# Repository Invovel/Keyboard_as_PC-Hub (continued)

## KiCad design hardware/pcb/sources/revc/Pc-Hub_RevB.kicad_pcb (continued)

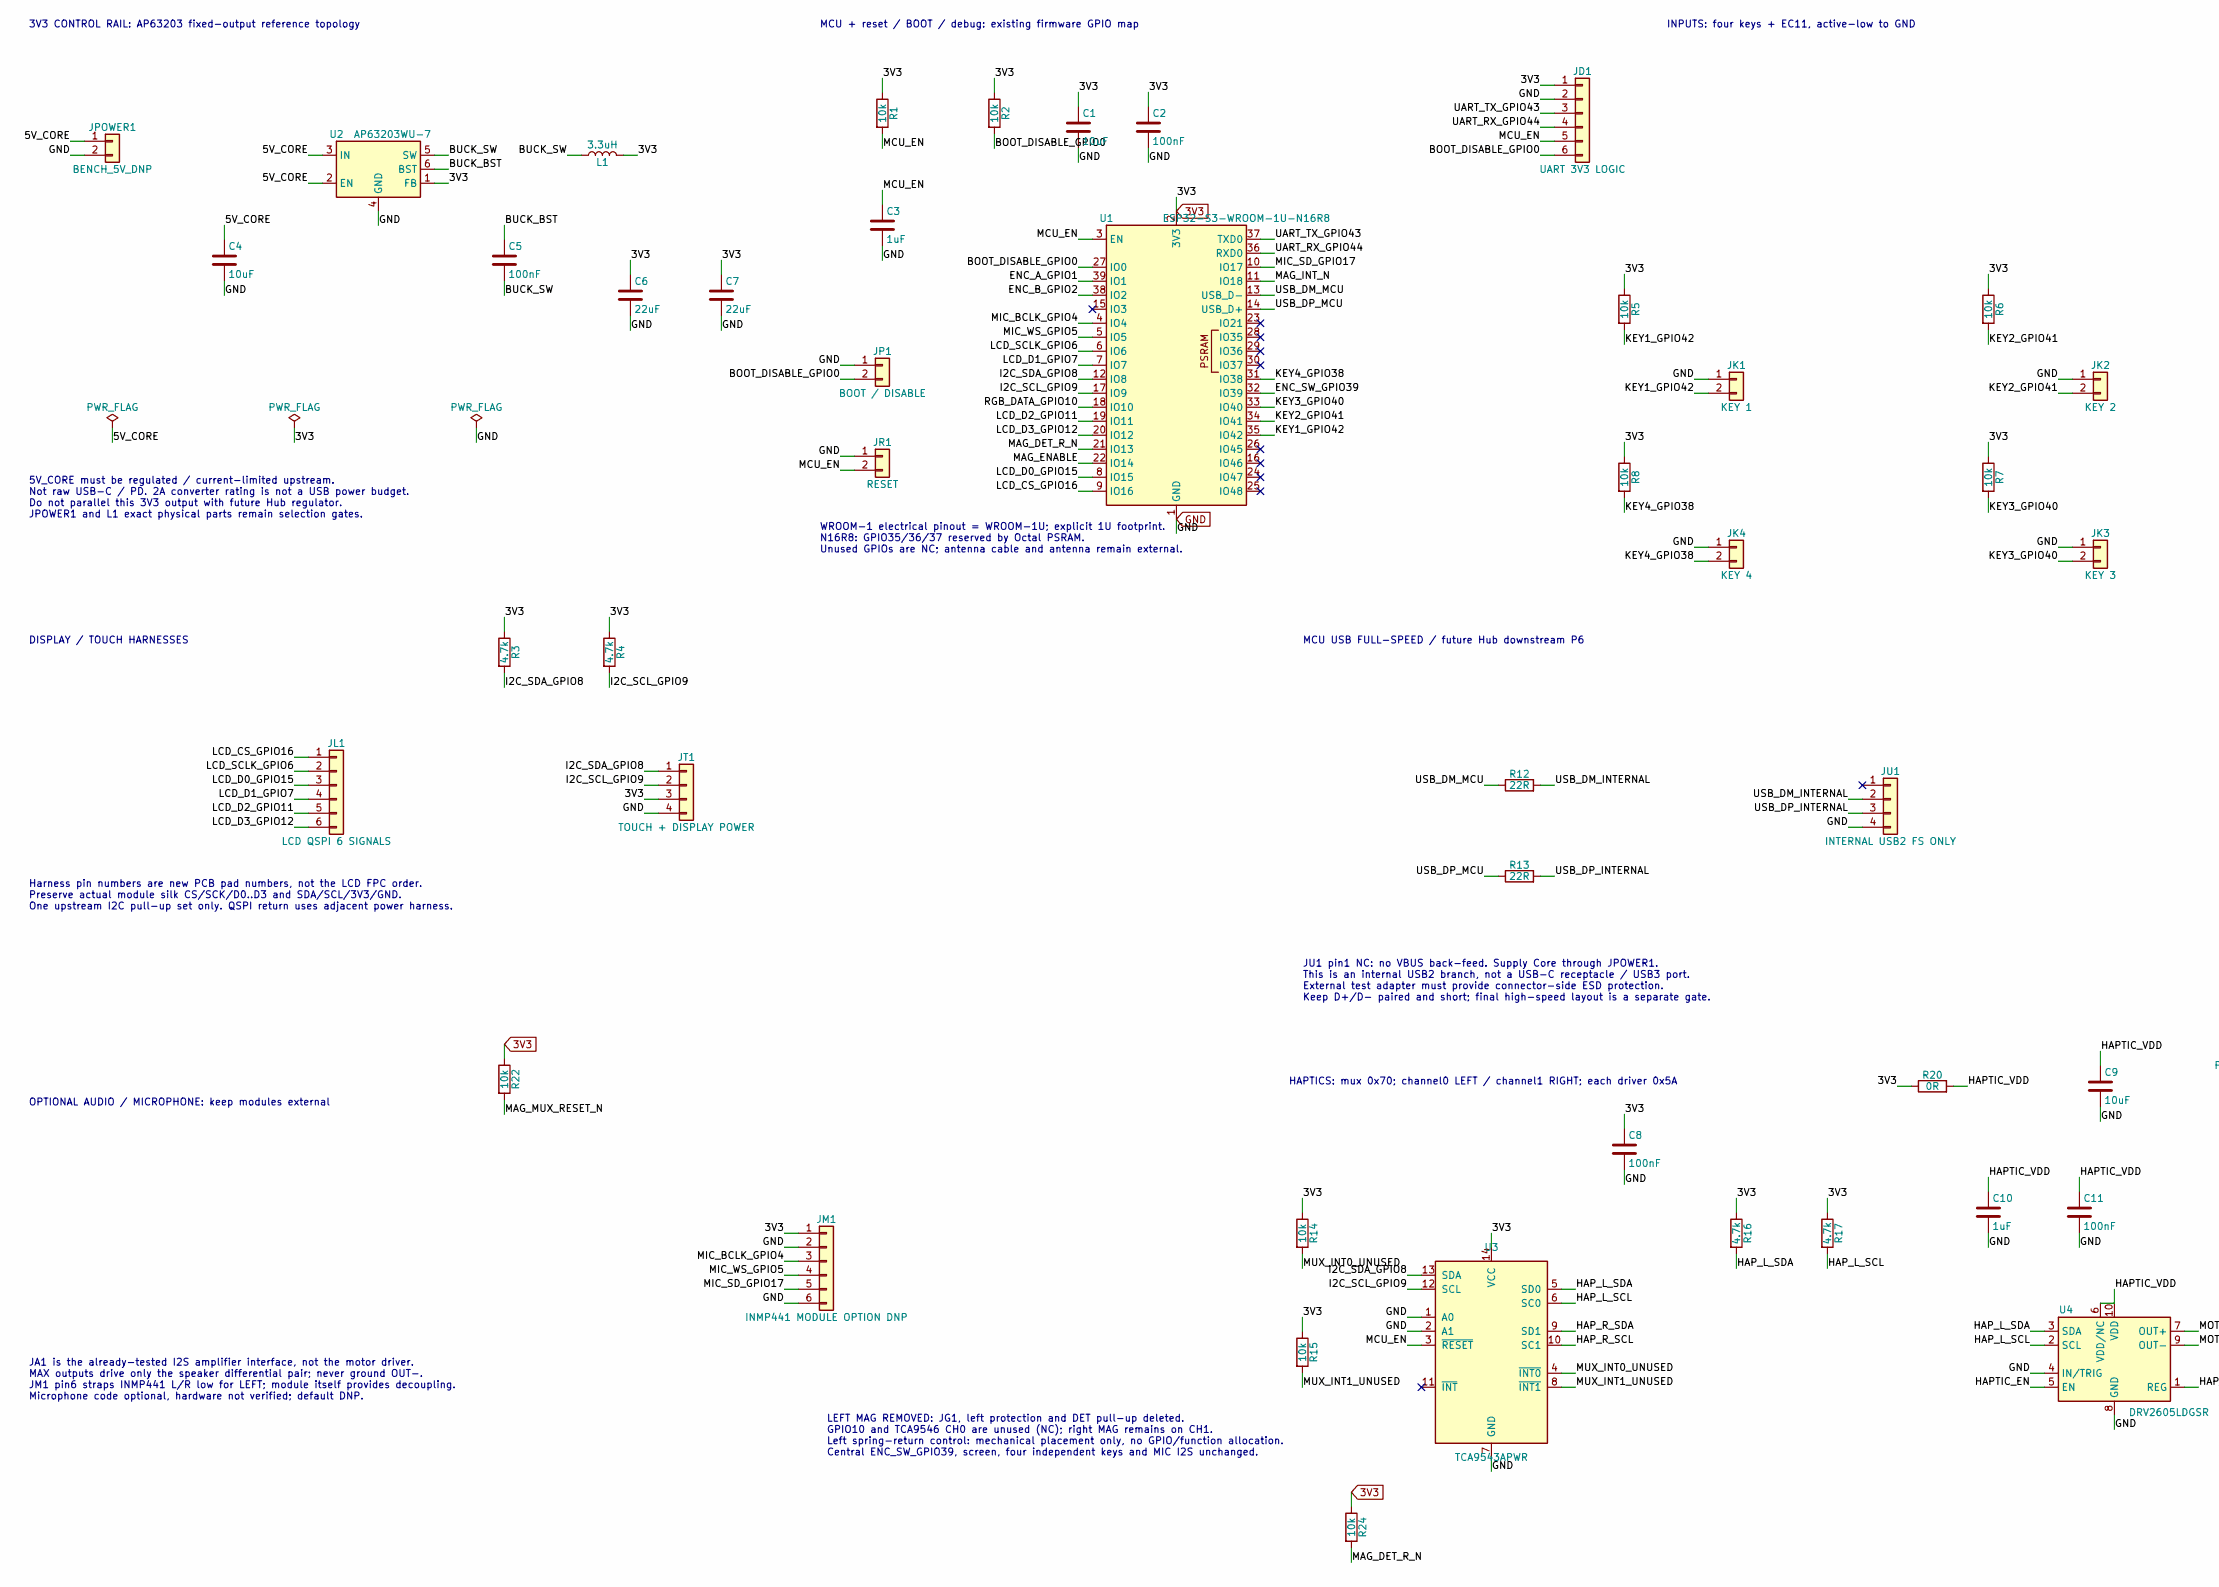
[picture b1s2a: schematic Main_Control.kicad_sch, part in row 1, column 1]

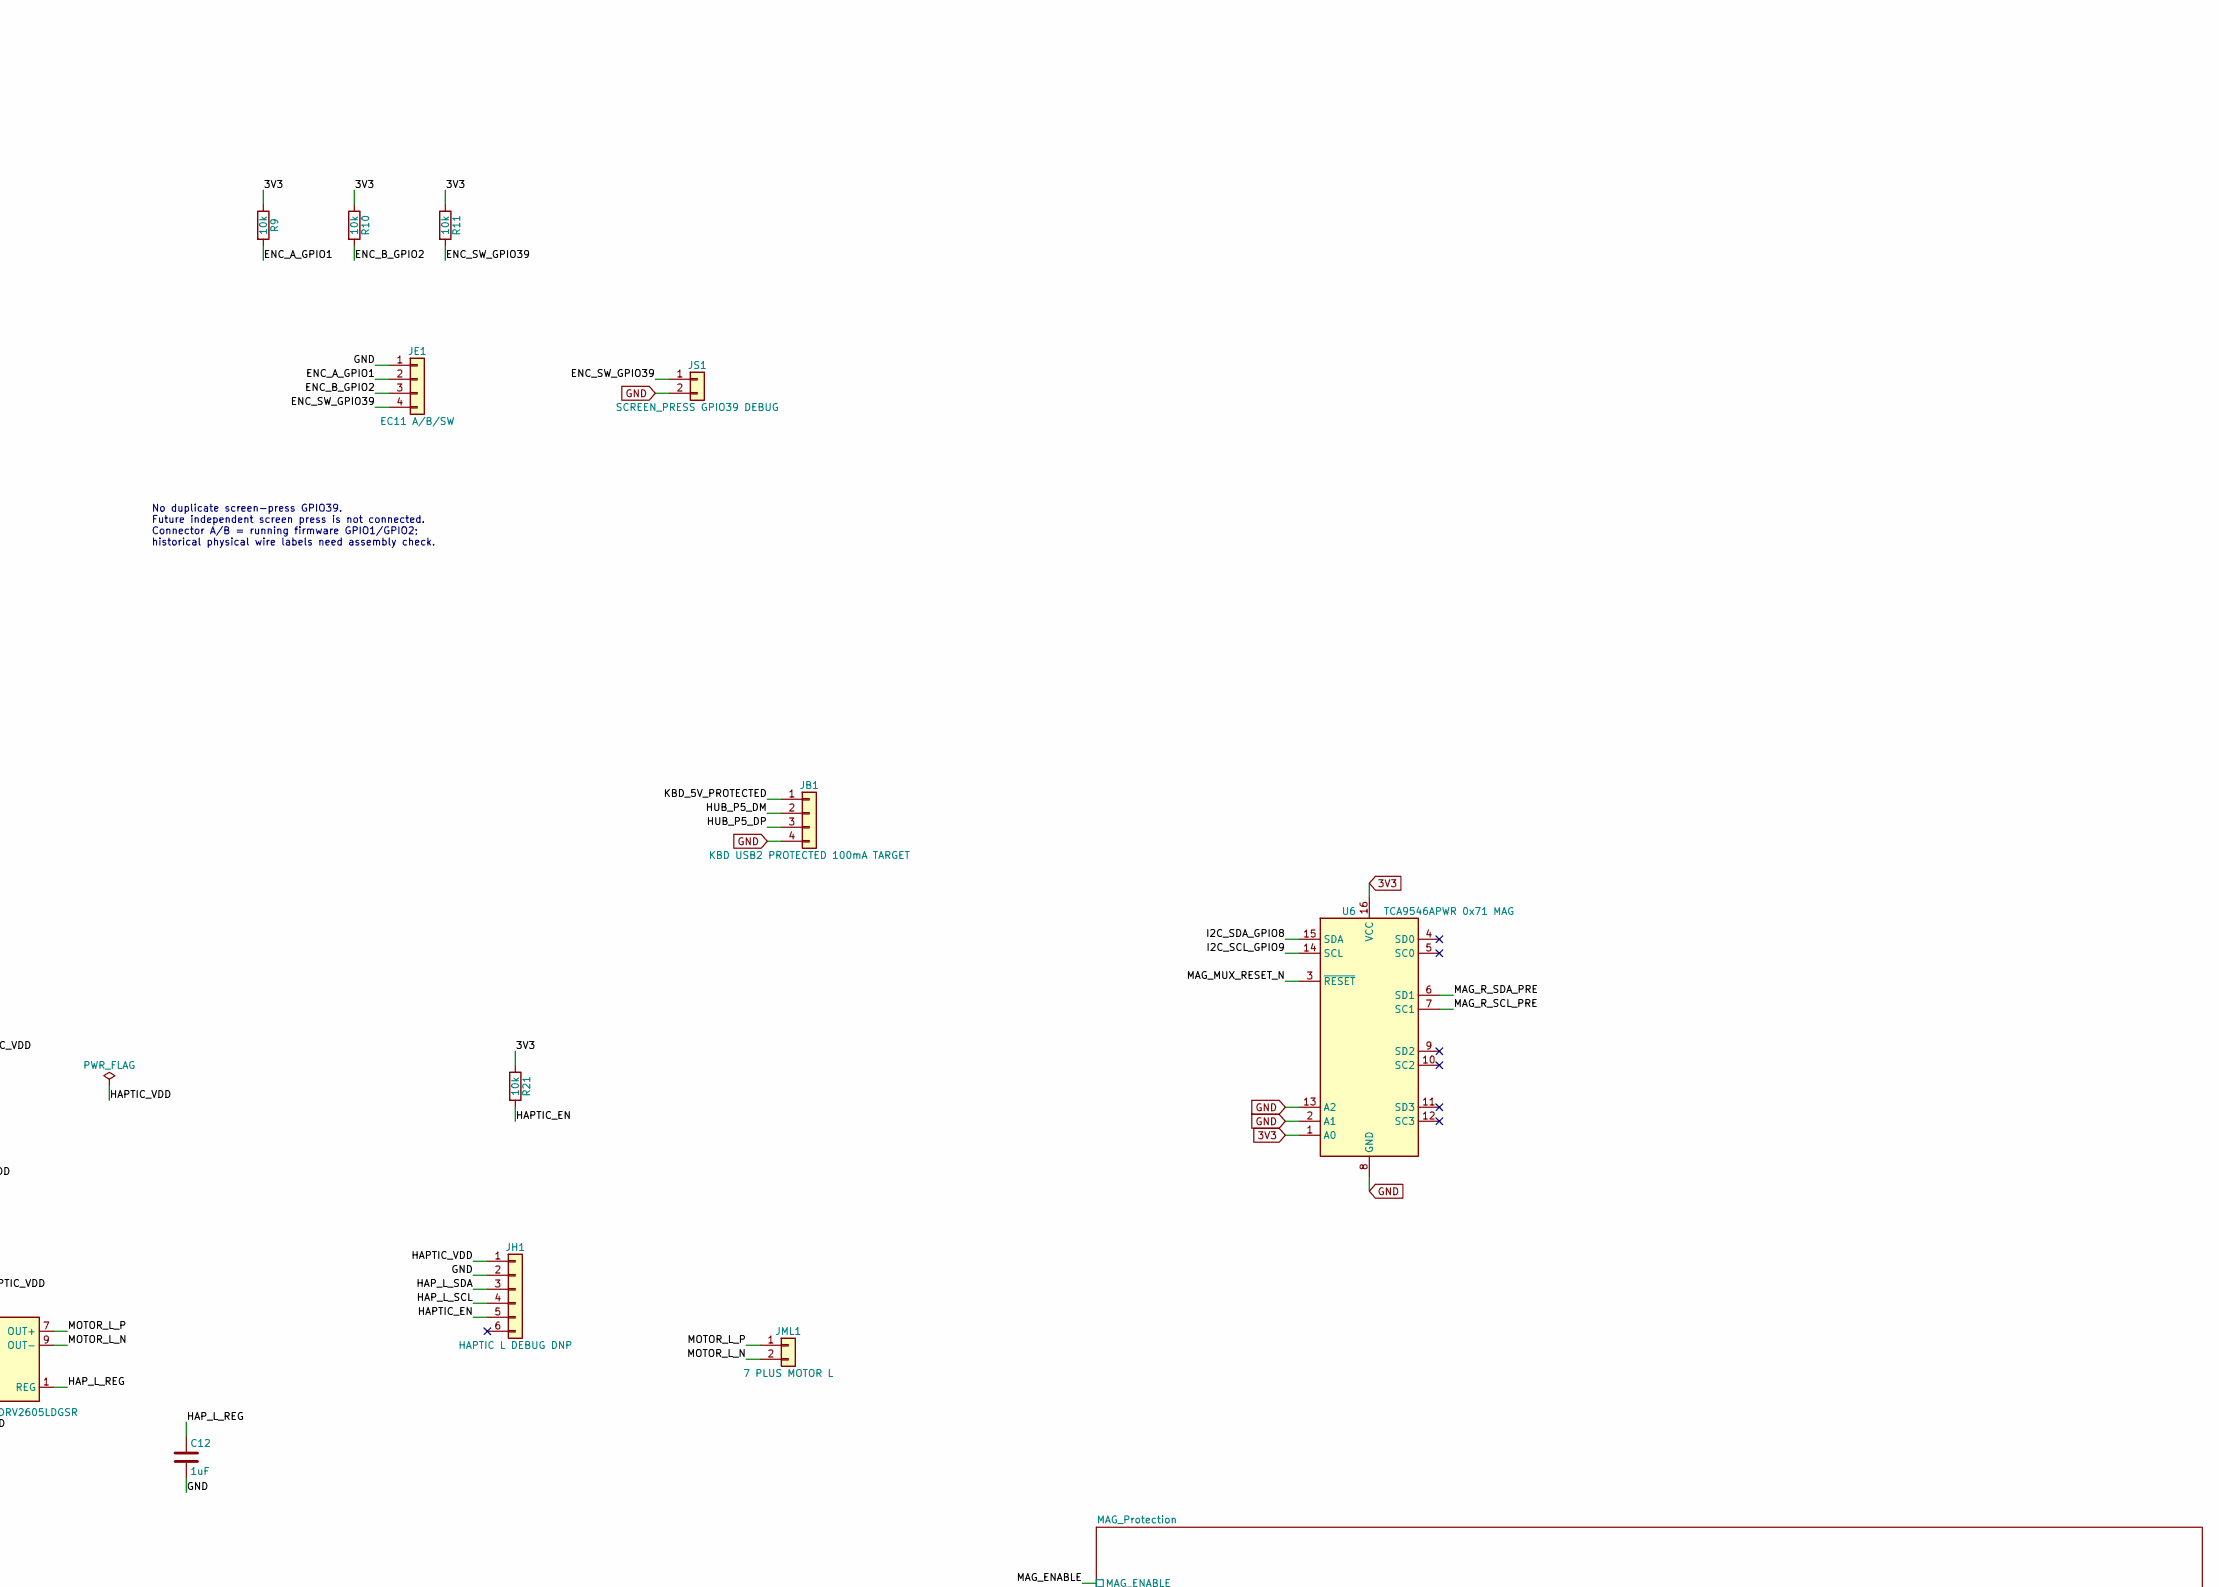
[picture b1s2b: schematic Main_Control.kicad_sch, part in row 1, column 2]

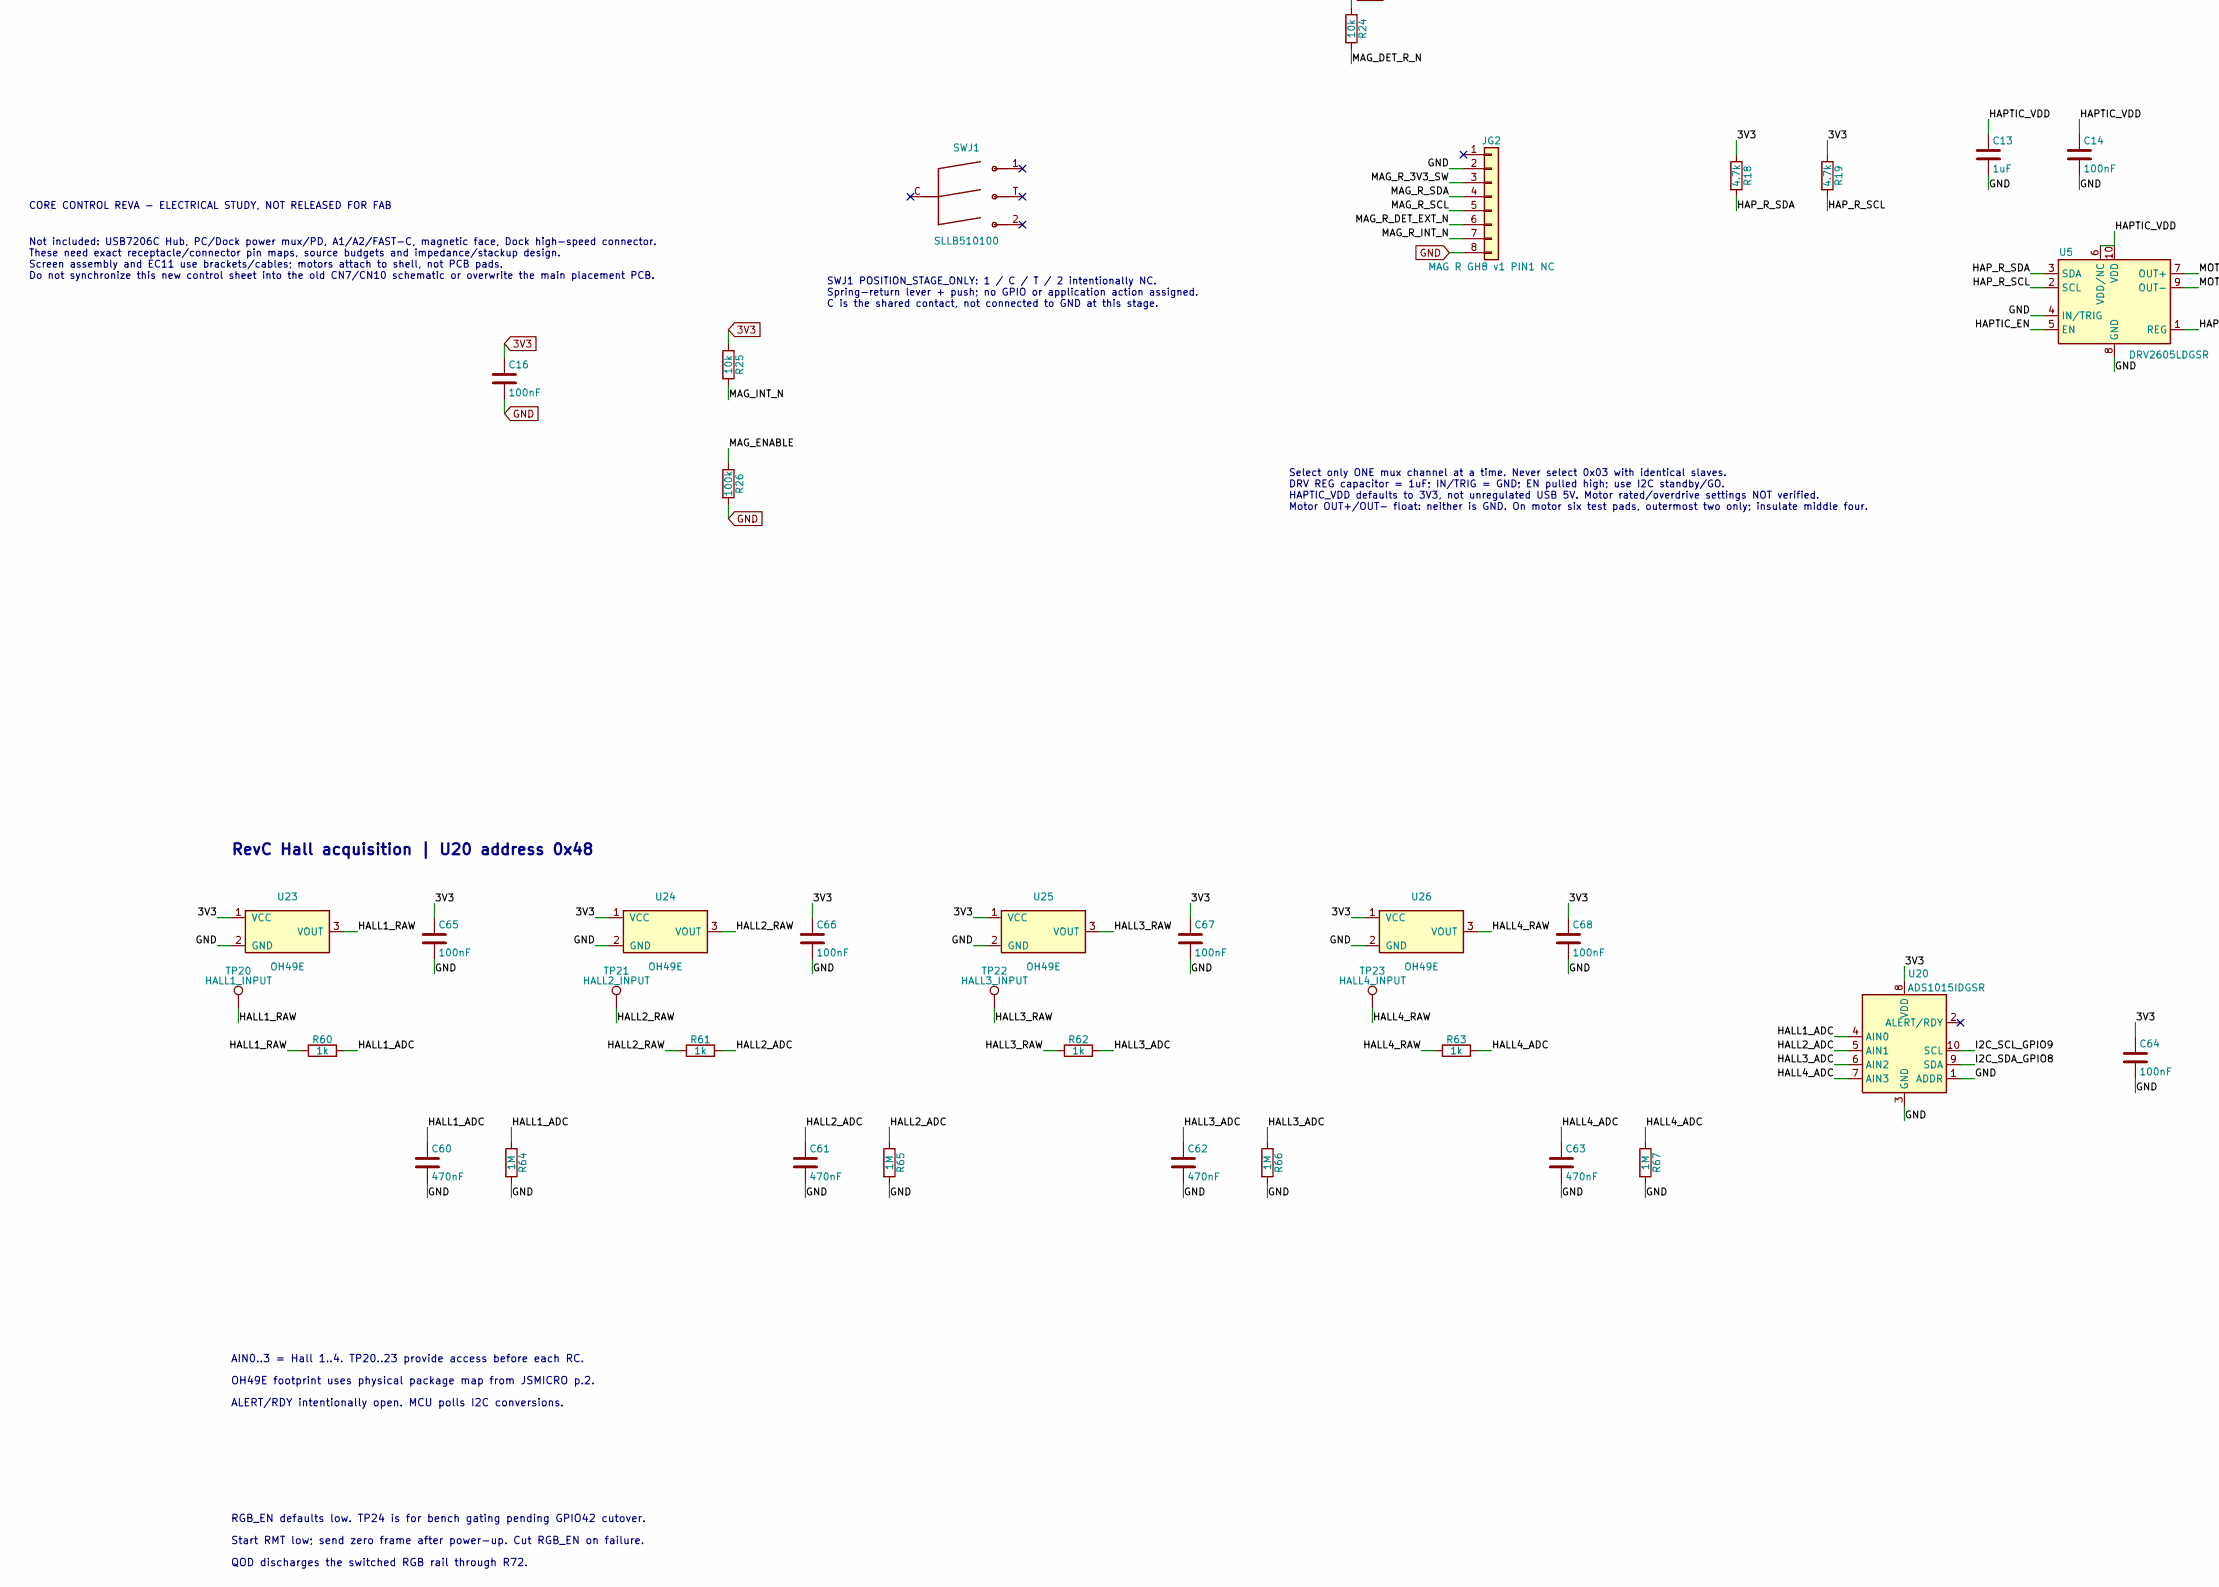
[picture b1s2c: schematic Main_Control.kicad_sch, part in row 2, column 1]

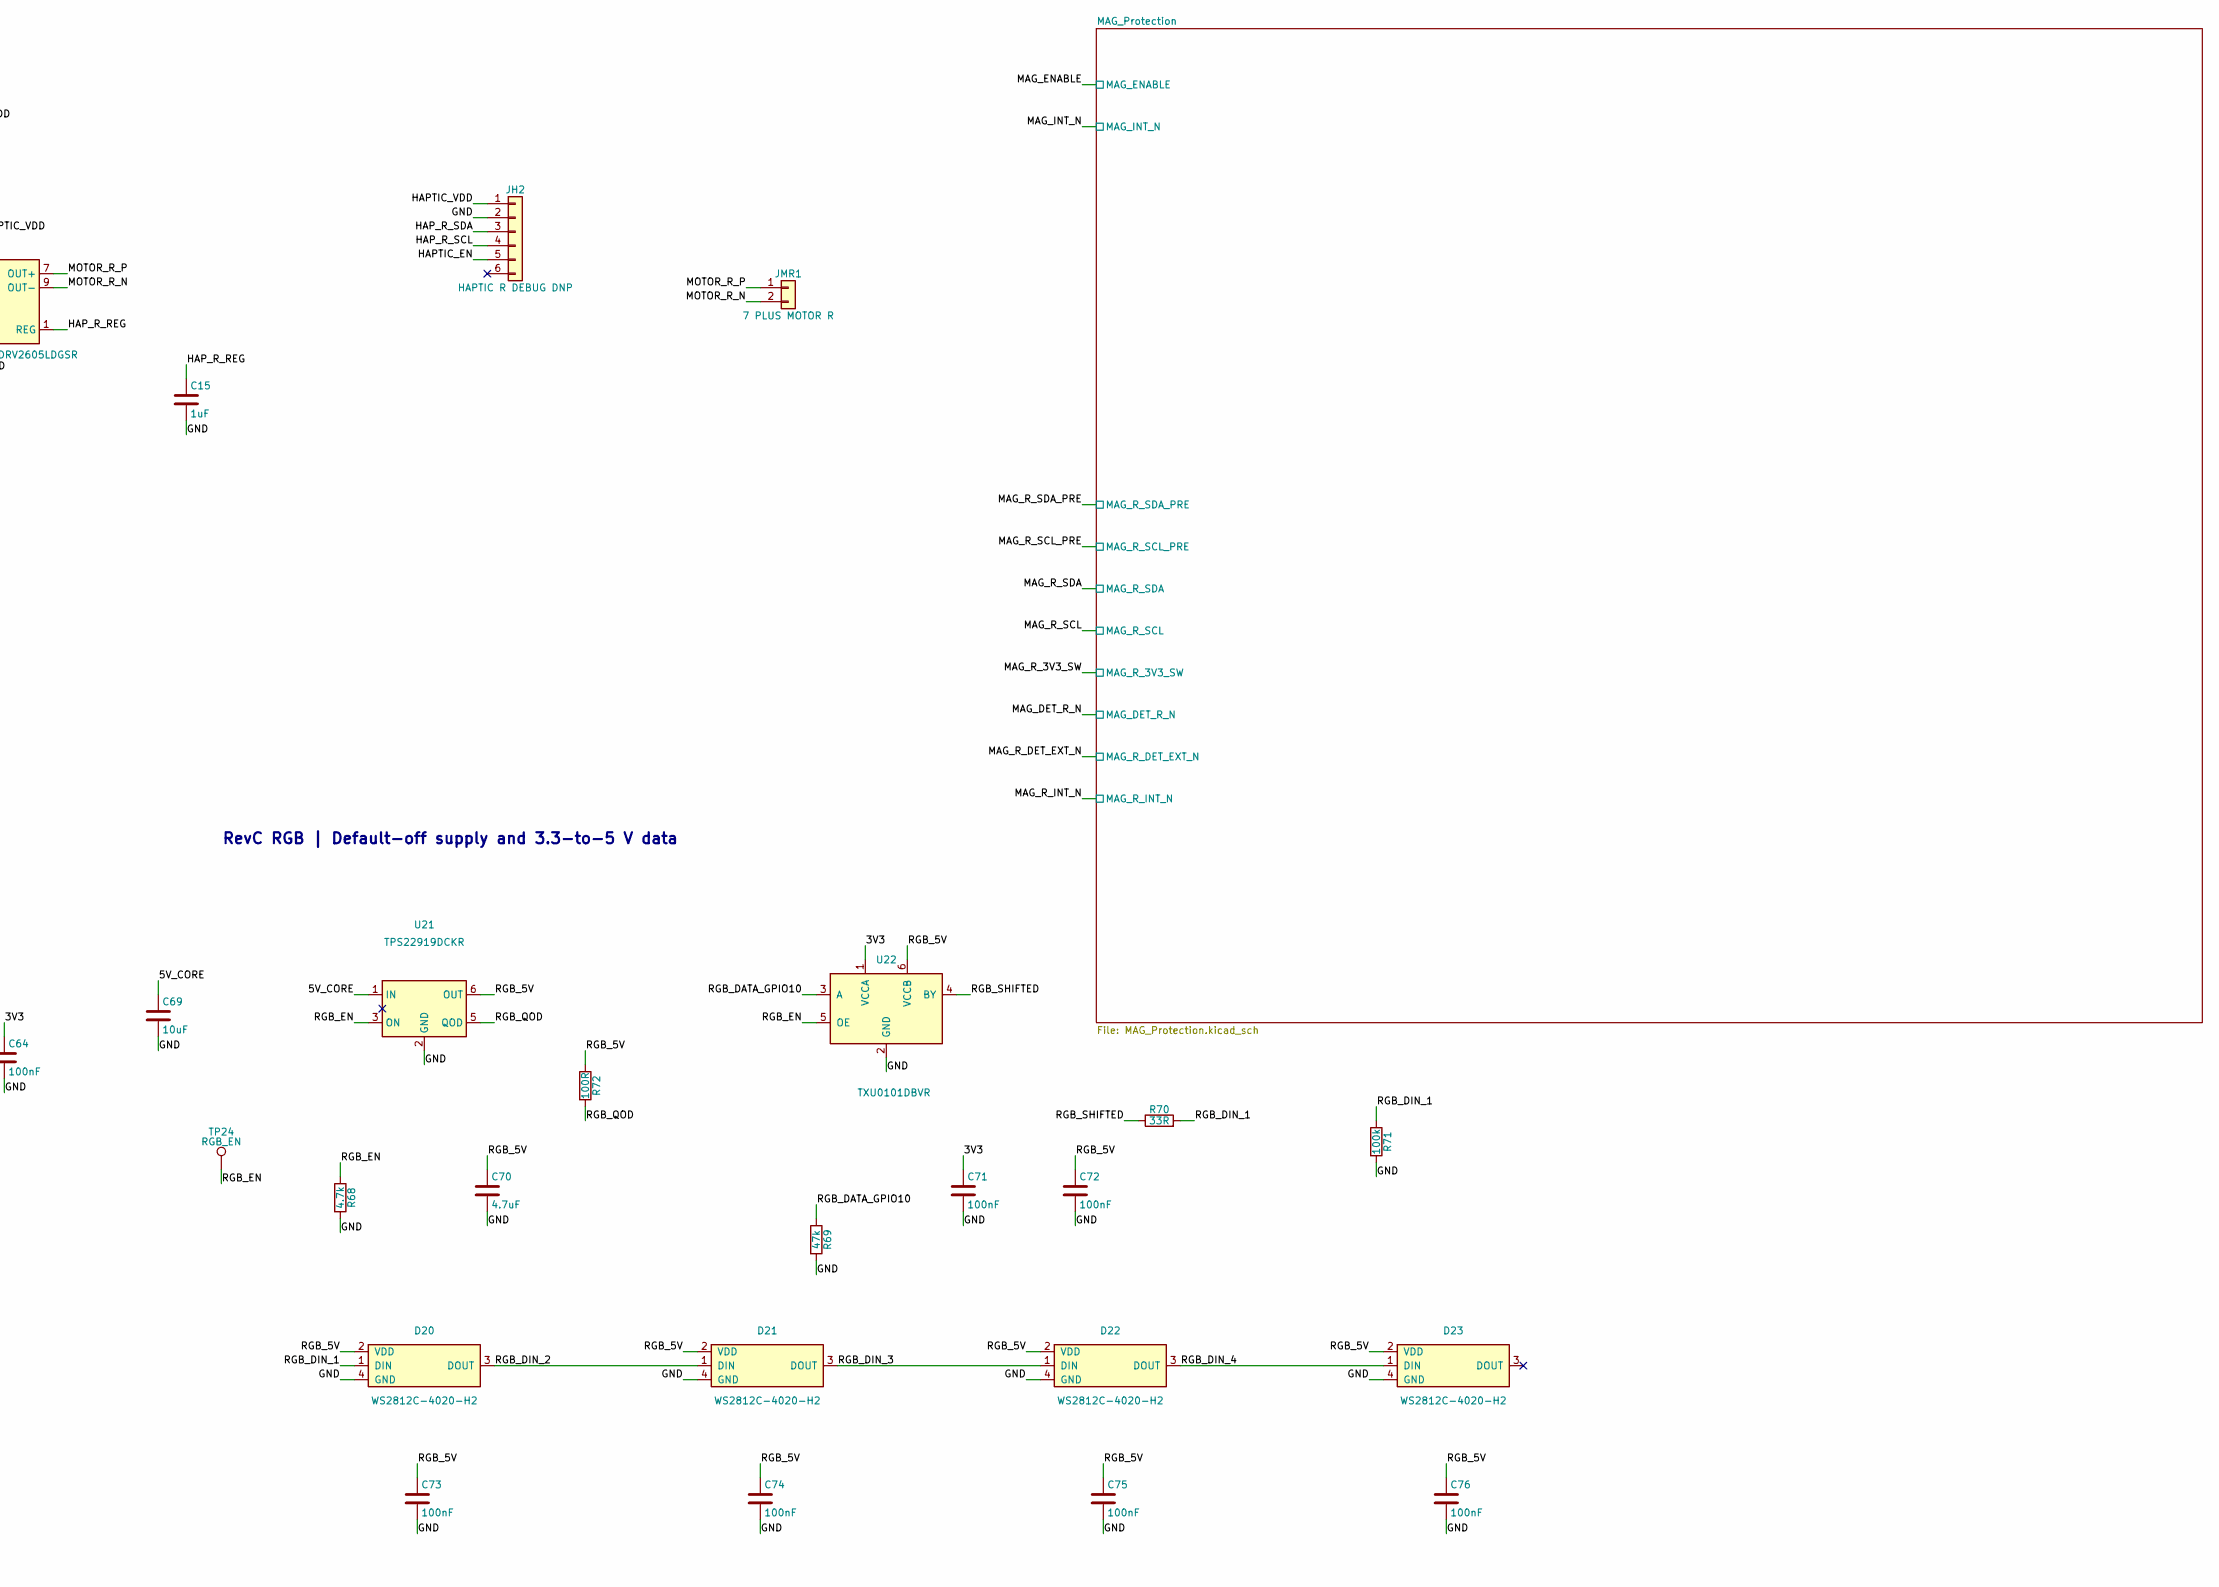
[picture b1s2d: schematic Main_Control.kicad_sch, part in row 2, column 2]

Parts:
C1, C9: 10uF; C_0805_2012Metric; Voltage 10V
C2, C5, C8, C11, C14: 100nF; C_0805_2012Metric; Voltage 16V
C3, C10, C12, C13, C15: 1uF; C_0805_2012Metric; Voltage 10V
C4: 10uF; C_0805_2012Metric; Voltage 16V
C6, C7: 22uF; C_0805_2012Metric; Voltage 10V
C16: 100nF; C_0402_1005Metric
C60, C61, C62, C63: 470nF; C_0603_1608Metric
C64, C65, C66, C67, C68, C71, C72, C73, C74, C75, C76: 100nF; C_0603_1608Metric
C69: 10uF; C_0805_2012Metric
C70: 4.7uF; C_0805_2012Metric
D20, D21, D22, D23: WS2812C-4020-H2; LED_Worldsemi_WS2812C-4020-H2; MPN WS2812C-4020-H2; LCSC C42417604
JB1: KBD USB2 PROTECTED 100mA TARGET; JST_GH_BM04B-GHS-TBT_1x04-1MP_P1.25mm_Vertical
JD1: UART 3V3 LOGIC; JST_GH_BM06B-GHS-TBT_1x06-1MP_P1.25mm_Vertical
JE1: EC11 A/B/SW; JST_GH_BM04B-GHS-TBT_1x04-1MP_P1.25mm_Vertical
JG2: MAG R GH8 v1 PIN1 NC; JST_GH_BM08B-GHS-TBT_1x08-1MP_P1.25mm_Vertical
JH1: HAPTIC L DEBUG DNP; JST_GH_BM06B-GHS-TBT_1x06-1MP_P1.25mm_Vertical
JH2: HAPTIC R DEBUG DNP; JST_GH_BM06B-GHS-TBT_1x06-1MP_P1.25mm_Vertical
JK1: KEY 1; JST_GH_BM02B-GHS-TBT_1x02-1MP_P1.25mm_Vertical
JK2: KEY 2; JST_GH_BM02B-GHS-TBT_1x02-1MP_P1.25mm_Vertical
JK3: KEY 3; JST_GH_BM02B-GHS-TBT_1x02-1MP_P1.25mm_Vertical
JK4: KEY 4; JST_GH_BM02B-GHS-TBT_1x02-1MP_P1.25mm_Vertical
JL1: LCD QSPI 6 SIGNALS; JST_GH_BM06B-GHS-TBT_1x06-1MP_P1.25mm_Vertical
JM1: INMP441 MODULE OPTION DNP; JST_GH_BM06B-GHS-TBT_1x06-1MP_P1.25mm_Vertical
JML1: 7 PLUS MOTOR L; JST_GH_BM02B-GHS-TBT_1x02-1MP_P1.25mm_Vertical
JMR1: 7 PLUS MOTOR R; JST_GH_BM02B-GHS-TBT_1x02-1MP_P1.25mm_Vertical
JP1: BOOT / DISABLE; JST_GH_BM02B-GHS-TBT_1x02-1MP_P1.25mm_Vertical
JPOWER1: BENCH_5V_DNP; Bench_5V_Input_2Pads_P5.08_D1.2; MPN PCB_DEFINED_FEATURE
JR1: RESET; JST_GH_BM02B-GHS-TBT_1x02-1MP_P1.25mm_Vertical
JS1: SCREEN_PRESS GPIO39 DEBUG; JST_GH_BM02B-GHS-TBT_1x02-1MP_P1.25mm_Vertical
JT1: TOUCH + DISPLAY POWER; JST_GH_BM04B-GHS-TBT_1x04-1MP_P1.25mm_Vertical
JU1: INTERNAL USB2 FS ONLY; JST_GH_BM04B-GHS-TBT_1x04-1MP_P1.25mm_Vertical
L1: 3.3uH; L_Bourns_SRP4020TA; MPN SRP4020TA-3R3M
R1, R2, R5, R6, R7, R8, R9, R10, R11, R14, R15, R21, R22, R24, R25: 10k; R_0603_1608Metric
R3, R4, R16, R17, R18, R19, R68: 4.7k; R_0603_1608Metric
R12, R13: 22R; R_0603_1608Metric
R20: 0R; R_1206_3216Metric
R26, R71: 100k; R_0603_1608Metric
R60, R61, R62, R63: 1k; R_0603_1608Metric
R64, R65, R66, R67: 1M; R_0603_1608Metric
R69: 47k; R_0603_1608Metric
R70: 33R; R_0603_1608Metric
R72: 100R; R_0603_1608Metric
SWJ1: SLLB510100; SW_Jog_ALPS_SLLB510100
TP20: HALL1_INPUT; TestPoint_Pad_D1.0mm
TP21: HALL2_INPUT; TestPoint_Pad_D1.0mm
TP22: HALL3_INPUT; TestPoint_Pad_D1.0mm
TP23: HALL4_INPUT; TestPoint_Pad_D1.0mm
TP24: RGB_EN; TestPoint_Pad_D1.0mm
U1: ESP32-S3-WROOM-1U-N16R8; ESP32-S3-WROOM-1U; MPN ESP32-S3-WROOM-1U-N16R8
U2: AP63203WU-7; TSOT-23-6; MPN AP63203WU-7
U3: TCA9543APWR; TSSOP-14_4.4x5mm_P0.65mm; MPN TCA9543APWR
U4, U5: DRV2605LDGSR; TSSOP-10_3x3mm_P0.5mm; MPN DRV2605LDGSR
U6: TCA9546APWR 0x71 MAG; TSSOP-16_4.4x5mm_P0.65mm
U20: ADS1015IDGSR; TSSOP-10_3x3mm_P0.5mm; MPN ADS1015IDGSR; LCSC C193969
U21: TPS22919DCKR; SOT-363_SC-70-6; MPN TPS22919DCKR
U22: TXU0101DBVR; SOT-23-6; MPN TXU0101DBVR
U23, U24, U25, U26: OH49E; SOT-23-3_JSMICRO_OH49E; MPN OH49E; LCSC C49021369

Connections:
3V3: C1.1, C2.1, C6.1, C7.1, C8.1, C16.1, C64.1, C65.1, C66.1, C67.1, C68.1, C71.1, JD1.1, JM1.1, JT1.3, L1.2, R1.1, R2.1, R3.1, R4.1, R5.1, R6.1, R7.1, R8.1, R9.1, R10.1, R11.1, R14.1, R15.1, R16.1, R17.1, R18.1, R19.1, R20.1, R21.1, R22.1, R24.1, R25.1, U1.2 (3V3), U2.1 (FB), U3.14 (VCC), U6.1 (A0), U6.16 (VCC), U20.8 (VDD), U22.1 (VCCA), U23.1 (VCC), U24.1 (VCC), U25.1 (VCC), U26.1 (VCC); also elsewhere on the board
/Main_Control/5V_CORE: C4.1, C69.1, JPOWER1.1, U2.2 (EN), U2.3 (IN), U21.1 (IN)
/Main_Control/BOOT_DISABLE_GPIO0: JD1.6, JP1.2, R2.2, U1.27 (IO0)
/Main_Control/BUCK_BST: C5.1, U2.6 (BST)
/Main_Control/BUCK_SW: C5.2, L1.1, U2.5 (SW)
/Main_Control/ENC_A_GPIO1: JE1.2, R9.2, U1.39 (IO1)
/Main_Control/ENC_B_GPIO2: JE1.3, R10.2, U1.38 (IO2)
/Main_Control/ENC_SW_GPIO39: JE1.4, JS1.1, R11.2, U1.32 (IO39)
/Main_Control/HALL1_ADC: C60.1, R60.2, R64.1, U20.4 (AIN0)
/Main_Control/HALL1_RAW: R60.1, TP20.1, U23.3 (VOUT)
/Main_Control/HALL2_ADC: C61.1, R61.2, R65.1, U20.5 (AIN1)
/Main_Control/HALL2_RAW: R61.1, TP21.1, U24.3 (VOUT)
/Main_Control/HALL3_ADC: C62.1, R62.2, R66.1, U20.6 (AIN2)
/Main_Control/HALL3_RAW: R62.1, TP22.1, U25.3 (VOUT)
/Main_Control/HALL4_ADC: C63.1, R63.2, R67.1, U20.7 (AIN3)
/Main_Control/HALL4_RAW: R63.1, TP23.1, U26.3 (VOUT)
/Main_Control/HAPTIC_EN: JH1.5, JH2.5, R21.2, U4.5 (EN), U5.5 (EN)
/Main_Control/HAPTIC_VDD: C9.1, C10.1, C11.1, C13.1, C14.1, JH1.1, JH2.1, R20.2, U4.6 (VDD/NC), U4.10 (VDD), U5.6 (VDD/NC), U5.10 (VDD)
/Main_Control/HAP_L_REG: C12.1, U4.1 (REG)
/Main_Control/HAP_L_SCL: JH1.4, R17.2, U3.6 (SC0), U4.2 (SCL)
/Main_Control/HAP_L_SDA: JH1.3, R16.2, U3.5 (SD0), U4.3 (SDA)
/Main_Control/HAP_R_REG: C15.1, U5.1 (REG)
/Main_Control/HAP_R_SCL: JH2.4, R19.2, U3.10 (SC1), U5.2 (SCL)
/Main_Control/HAP_R_SDA: JH2.3, R18.2, U3.9 (SD1), U5.3 (SDA)
/Main_Control/HUB_P5_DM: JB1.2
/Main_Control/HUB_P5_DP: JB1.3
/Main_Control/I2C_SCL_GPIO9: JT1.2, R4.2, U1.17 (IO9), U3.12 (SCL), U6.14 (SCL), U20.10 (SCL)
/Main_Control/I2C_SDA_GPIO8: JT1.1, R3.2, U1.12 (IO8), U3.13 (SDA), U6.15 (SDA), U20.9 (SDA)
/Main_Control/KBD_5V_PROTECTED: JB1.1
/Main_Control/KEY2_GPIO41: JK2.2, R6.2, SWJ1.2 (CW), U1.34 (IO41)
/Main_Control/KEY3_GPIO40: JK3.2, R7.2, SWJ1.T (PUSH), U1.33 (IO40)
/Main_Control/KEY4_GPIO38: JK4.2, R8.2, SWJ1.1 (CCW), U1.31 (IO38)
/Main_Control/LCD_CS_GPIO16: JL1.1, U1.9 (IO16)
/Main_Control/LCD_D0_GPIO15: JL1.3, U1.8 (IO15)
/Main_Control/LCD_D1_GPIO7: JL1.4, U1.7 (IO7)
/Main_Control/LCD_D2_GPIO11: JL1.5, U1.19 (IO11)
/Main_Control/LCD_D3_GPIO12: JL1.6, U1.20 (IO12)
/Main_Control/LCD_SCLK_GPIO6: JL1.2, U1.6 (IO6)
/Main_Control/MAG_DET_R_N: R24.2, U1.21 (IO13); also elsewhere on the board
/Main_Control/MAG_ENABLE: R26.1, U1.22 (IO14); also elsewhere on the board
/Main_Control/MAG_INT_N: R25.2, U1.11 (IO18); also elsewhere on the board
/Main_Control/MAG_MUX_RESET_N: R22.2, U6.3 (~RESET)
/Main_Control/MAG_R_3V3_SW: JG2.3; also elsewhere on the board
/Main_Control/MAG_R_DET_EXT_N: JG2.6; also elsewhere on the board
/Main_Control/MAG_R_INT_N: JG2.7; also elsewhere on the board
/Main_Control/MAG_R_SCL: JG2.5; also elsewhere on the board
/Main_Control/MAG_R_SCL_PRE: U6.7 (SC1); also elsewhere on the board
/Main_Control/MAG_R_SDA: JG2.4; also elsewhere on the board
/Main_Control/MAG_R_SDA_PRE: U6.6 (SD1); also elsewhere on the board
/Main_Control/MCU_EN: C3.1, JD1.5, JR1.2, R1.2, U1.3 (EN), U3.3 (~RESET)
/Main_Control/MIC_BCLK_GPIO4: JM1.3, U1.4 (IO4)
/Main_Control/MIC_SD_GPIO17: JM1.5, U1.10 (IO17)
/Main_Control/MIC_WS_GPIO5: JM1.4, U1.5 (IO5)
/Main_Control/MOTOR_L_N: JML1.2, U4.9 (OUT-)
/Main_Control/MOTOR_L_P: JML1.1, U4.7 (OUT+)
/Main_Control/MOTOR_R_N: JMR1.2, U5.9 (OUT-)
/Main_Control/MOTOR_R_P: JMR1.1, U5.7 (OUT+)
/Main_Control/MUX_INT0_UNUSED: R14.2, U3.4 (~INT0)
/Main_Control/MUX_INT1_UNUSED: R15.2, U3.8 (~INT1)
/Main_Control/RGB_5V: C70.1, C72.1, C73.1, C74.1, C75.1, C76.1, D20.2 (VDD), D21.2 (VDD), D22.2 (VDD), D23.2 (VDD), R72.1, U21.6 (OUT), U22.6 (VCCB)
/Main_Control/RGB_DATA_GPIO10: R69.1, U1.18 (IO10), U22.3 (A)
/Main_Control/RGB_DIN_1: D20.1 (DIN), R70.2, R71.1
/Main_Control/RGB_DIN_2: D20.3 (DOUT), D21.1 (DIN)
/Main_Control/RGB_DIN_3: D21.3 (DOUT), D22.1 (DIN)
/Main_Control/RGB_DIN_4: D22.3 (DOUT), D23.1 (DIN)
/Main_Control/RGB_QOD: R72.2, U21.5 (QOD)
/Main_Control/RGB_SHIFTED: R70.1, U22.4 (BY)
/Main_Control/UART_RX_GPIO44: JD1.4, U1.36 (RXD0)
/Main_Control/UART_TX_GPIO43: JD1.3, U1.37 (TXD0)
/Main_Control/USB_DM_INTERNAL: JU1.2, R12.2
/Main_Control/USB_DM_MCU: R12.1, U1.13 (USB_D-)
/Main_Control/USB_DP_INTERNAL: JU1.3, R13.2
/Main_Control/USB_DP_MCU: R13.1, U1.14 (USB_D+)
GND: C1.2, C2.2, C3.2, C4.2, C6.2, C7.2, C8.2, C9.2, C10.2, C11.2, C12.2, C13.2, C14.2, C15.2, C16.2, C60.2, C61.2, C62.2, C63.2, C64.2, C65.2, C66.2, C67.2, C68.2, C69.2, C70.2, C71.2, C72.2, C73.2, C74.2, C75.2, C76.2, D20.4 (GND), D21.4 (GND), D22.4 (GND), D23.4 (GND), JB1.4, JD1.2, JE1.1, JG2.2, JG2.8, JH1.2, JH2.2, JK1.1, JK2.1, JK3.1, JK4.1, JM1.2, JM1.6, JP1.1, JPOWER1.2, JR1.1, JS1.2, JT1.4, JU1.4, R26.2, R64.2, R65.2, R66.2, R67.2, R68.2, R69.2, R71.2, SWJ1.C (COMMON), U1.1 (GND), U1.40 (GND), U1.41 (GND), U2.4 (GND), U3.1 (A0), U3.2 (A1), U3.7 (GND), U4.4 (IN/TRIG), U4.8 (GND), U5.4 (IN/TRIG), U5.8 (GND), U6.2 (A1), U6.8 (GND), U6.13 (A2), U20.1 (ADDR), U20.3 (GND), U21.2 (GND), U22.2 (GND), U23.2 (GND), U24.2 (GND), U25.2 (GND), U26.2 (GND); also elsewhere on the board

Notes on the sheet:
MCU + reset / BOOT / debug: existing firmware GPIO map
INPUTS: four keys + EC11, active-low to GND
5V_CORE must be regulated / current-limited upstream. Not raw USB-C / PD. 2A converter rating is not a USB power budget. Do not parallel this 3V3 output with future Hub regulator. JPOWER1 and L1 exact physical parts remain selection gates.
Harness pin numbers are new PCB pad numbers, not the LCD FPC order. Preserve actual module silk CS/SCK/D0..D3 and SDA/SCL/3V3/GND. One upstream I2C pull-up set only. QSPI return uses adjacent power harness.
CORE CONTROL REVA - ELECTRICAL STUDY, NOT RELEASED FOR FAB
MCU USB FULL-SPEED / future Hub downstream P6
3V3 CONTROL RAIL: AP63203 fixed-output reference topology
SWJ1 POSITION_STAGE_ONLY: 1 / C / T / 2 intentionally NC. Spring-return lever + push; no GPIO or application action assigned. C is the shared contact, not connected to GND at this stage.
JU1 pin1 NC: no VBUS back-feed. Supply Core through JPOWER1. This is an internal USB2 branch, not a USB-C receptacle / USB3 port. External test adapter must provide connector-side ESD protection. Keep D+/D- paired and short; final high-speed layout is a separate gate.
Select only ONE mux channel at a time. Never select 0x03 with identical slaves. DRV REG capacitor = 1uF; IN/TRIG = GND; EN pulled high; use I2C standby/GO. HAPTIC_VDD defaults to 3V3, not unregulated USB 5V. Motor rated/overdrive settings NOT verified. Motor OUT+/OUT- float: neither is GND. On moto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
Not included: USB7206C Hub, PC/Dock power mux/PD, A1/A2/FAST-C, magnetic face, Dock high-speed connector. These need exact receptacle/connector pin maps, source budgets and impedance/stackup design. Screen assembly and EC11 use brackets/cables; motors attach to shell, not PCB pads. Do not synchroni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
WROOM-1 electrical pinout = WROOM-1U; explicit 1U footprint. N16R8: GPIO35/36/37 reserved by Octal PSRAM. Unused GPIOs are NC; antenna cable and antenna remain external.
HAPTICS: mux 0x70; channel0 LEFT / channel1 RIGHT; each driver 0x5A
No duplicate screen-press GPIO39. Future independent screen press is not connected. Connector A/B = running firmware GPIO1/GPIO2; historical physical wire labels need assembly check.
LEFT MAG REMOVED: JG1, left protection and DET pull-up deleted. GPIO10 and TCA9546 CH0 are unused (NC); right MAG remains on CH1. Left spring-return control: mechanical placement only, no GPIO/function allocation. Central ENC_SW_GPIO39, screen, four independent keys and MIC I2S unchanged.
JA1 is the already-tested I2S amplifier interface, not the motor driver. MAX outputs drive only the speaker differential pair; never ground OUT-. JM1 pin6 straps INMP441 L/R low for LEFT; module itself provides decoupling. Microphone code optional, hardware not verified; default DNP.
OPTIONAL AUDIO / MICROPHONE: keep modules external
DISPLAY / TOUCH HARNESSES
RevC Hall acquisition | U20 address 0x48
AIN0..3 = Hall 1..4. TP20..23 provide access before each RC.
OH49E footprint uses physical package map from JSMICRO p.2.
ALERT/RDY intentionally open. MCU polls I2C conversions.
RevC RGB | Default-off supply and 3.3-to-5 V data
RGB_EN defaults low. TP24 is for bench gating pending GPIO42 cutover.
Start RMT low; send zero frame after power-up. Cut RGB_EN on failure.
QOD discharges the switched RGB rail through R72.

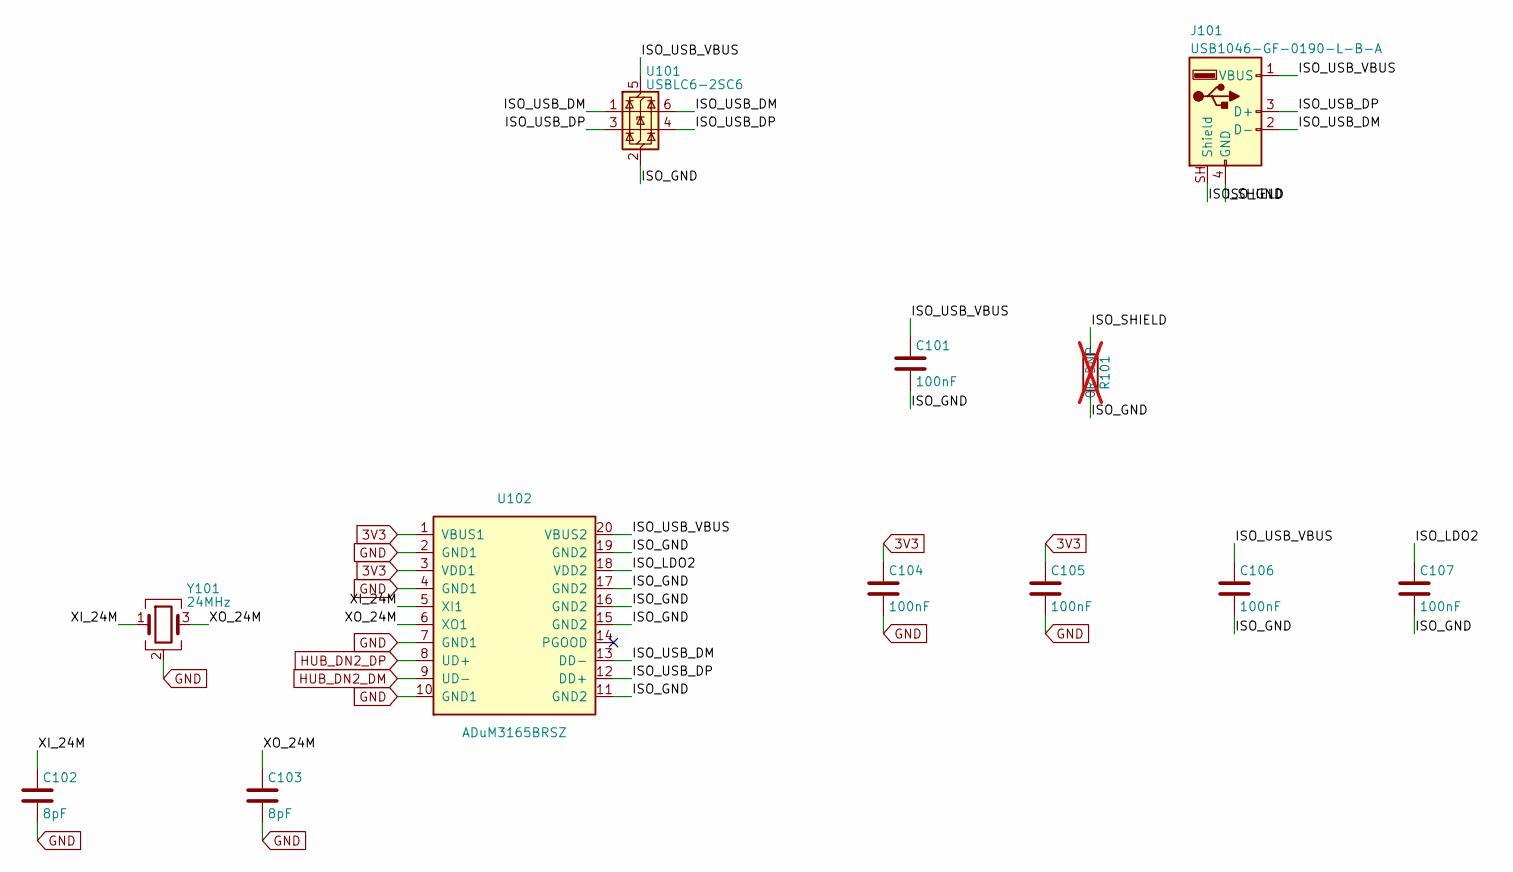
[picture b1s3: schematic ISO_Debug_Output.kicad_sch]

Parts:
C101: 100nF; C_0805_2012Metric
C102, C103: 8pF; C_0402_1005Metric
C104, C105, C106, C107: 100nF; C_0402_1005Metric
J101: USB1046-GF-0190-L-B-A; USB_A_Receptacle_GCT_USB1046
R101: 0R DNP; R_0603_1608Metric; not fitted
U101: USBLC6-2SC6; SOT-23-6
U102: ADuM3165BRSZ; SSOP-20_5.3x7.2mm_P0.65mm
Y101: 24MHz; Crystal_SMD_2016-4Pin_2.0x1.6mm

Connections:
3V3: C104.1, C105.1, U102.1 (VBUS1), U102.3 (VDD1); also elsewhere on the board
/ISO_Debug_Output/ISO_GND: C101.2, C106.2, C107.2, J101.4 (GND), R101.2, U101.2 (GND), U102.11 (GND2), U102.15 (GND2), U102.16 (GND2), U102.17 (GND2), U102.19 (GND2)
/ISO_Debug_Output/ISO_LDO2: C107.1, U102.18 (VDD2)
/ISO_Debug_Output/ISO_SHIELD: J101.SH (Shield), R101.1
/ISO_Debug_Output/ISO_USB_DM: J101.2 (D-), U101.1 (I/O1), U101.6 (I/O1), U102.13 (DD-)
/ISO_Debug_Output/ISO_USB_DP: J101.3 (D+), U101.3 (I/O2), U101.4 (I/O2), U102.12 (DD+)
/ISO_Debug_Output/ISO_USB_VBUS: C101.1, C106.1, J101.1 (VBUS), U101.5 (VBUS), U102.20 (VBUS2)
/ISO_Debug_Output/XI_24M: C102.1, U102.5 (XI1), Y101.1
/ISO_Debug_Output/XO_24M: C103.1, U102.6 (XO1), Y101.3
GND: C102.2, C103.2, C104.2, C105.2, U102.2 (GND1), U102.4 (GND1), U102.7 (GND1), U102.10 (GND1), Y101.2 (G), Y101.4 (G); also elsewhere on the board
HUB_DN2_DM: U102.9 (UD-)
HUB_DN2_DP: U102.8 (UD+)
